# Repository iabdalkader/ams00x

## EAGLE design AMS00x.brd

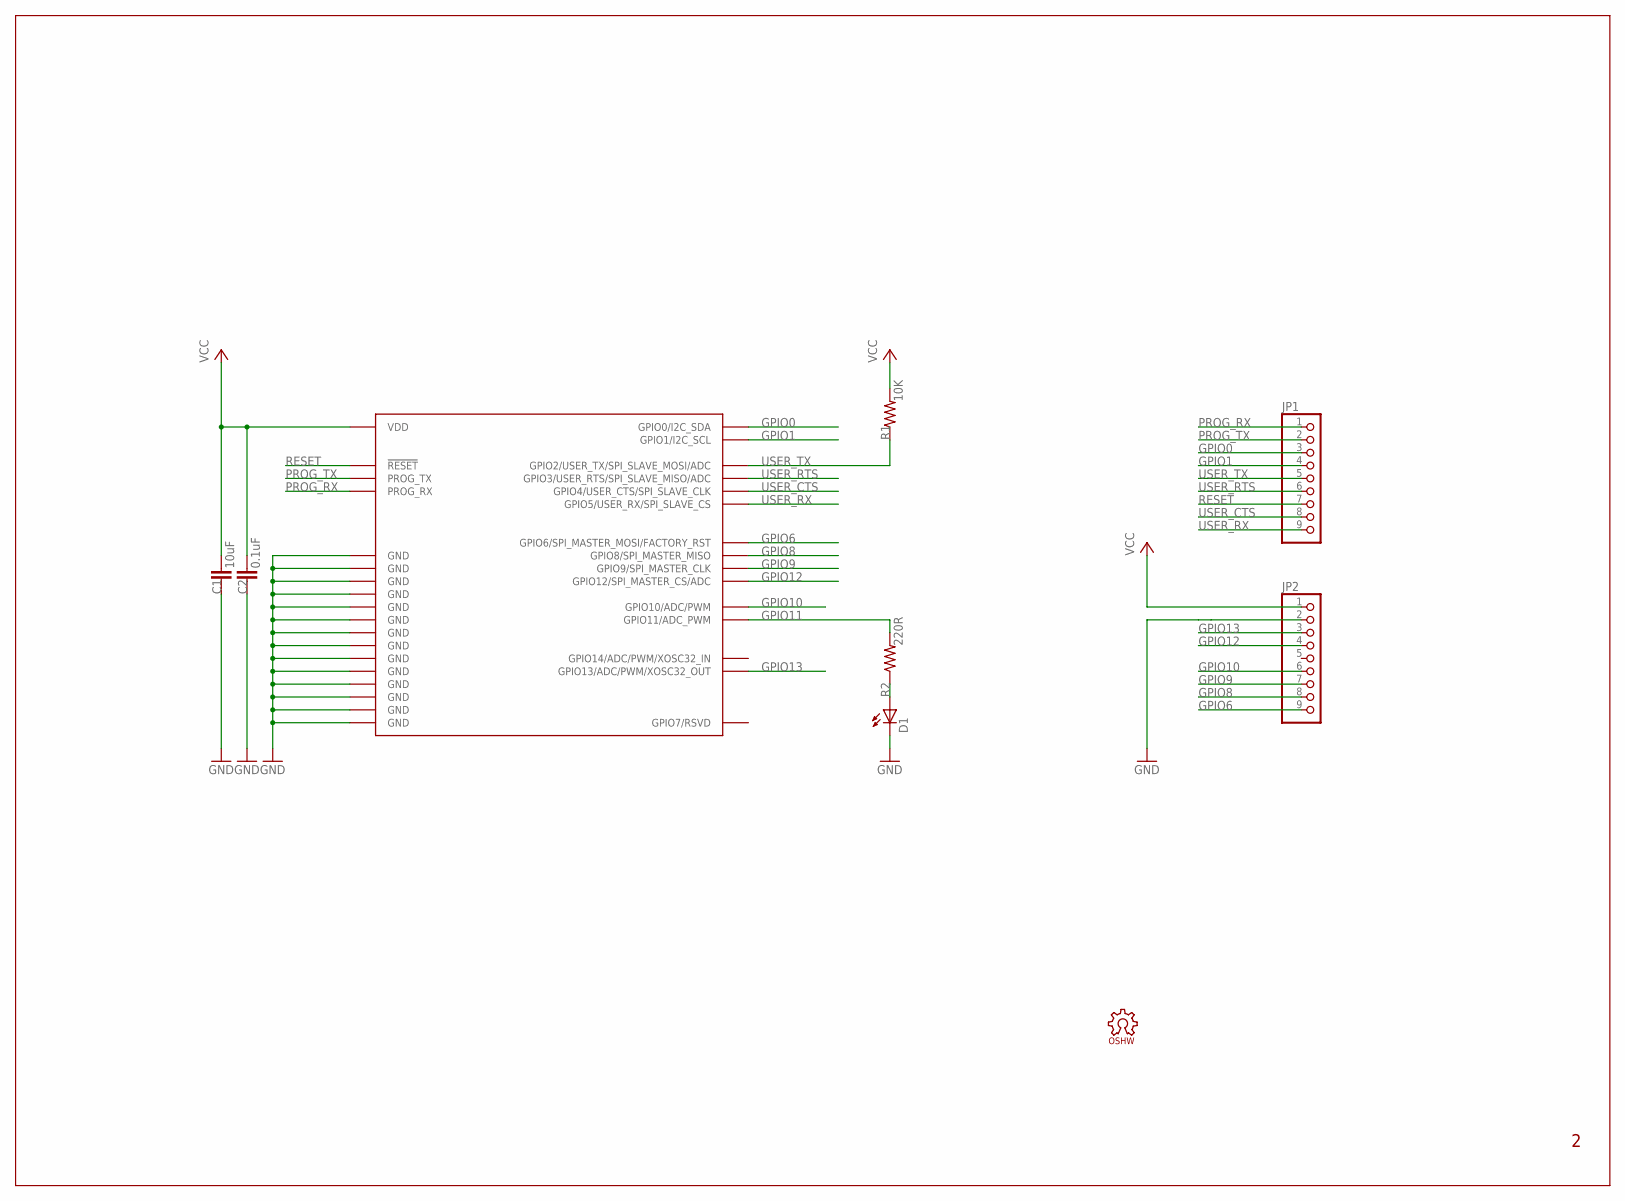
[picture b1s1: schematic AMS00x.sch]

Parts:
C1: 10uF; 0603-CAP
C2: 0.1uF; 0603-CAP
D1: LED0603; LED-0603
JP1, JP2: PINHD-1X9; 1X09
LOGO1: OSHW_LOGO_6MILX0100-NT; OSHW_6X100_NOTEXT
R1: 10K; 0603-RES
R2: 220R; 0603-RES
U$3: AMS00X

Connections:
GND: C1.1, C2.1, D1.C, JP2.2, U$3.P$1 (GND), U$3.P$19 (GND), U$3.P$22 (GND), U$3.P$23 (GND), U$3.P$24 (GND), U$3.P$25 (GND), U$3.P$26 (GND), U$3.P$27 (GND), U$3.P$28 (GND), U$3.P$29 (GND), U$3.P$30 (GND), U$3.P$31 (GND), U$3.P$32 (GND), U$3.P$33 (GND)
GPIO0: JP1.3, U$3.P$4 (GPIO0/I2C_SDA)
GPIO1: JP1.4, U$3.P$5 (GPIO1/I2C_SCL)
GPIO6: JP2.9, U$3.P$11 (GPIO6/SPI_MASTER_MOSI/FACTORY_RST)
GPIO8: JP2.8, U$3.P$13 (GPIO8/SPI_MASTER_MISO)
GPIO9: JP2.7, U$3.P$14 (GPIO9/SPI_MASTER_CLK)
GPIO10: JP2.6, U$3.P$15 (GPIO10/ADC/PWM)
GPIO11: R2.2, U$3.P$16 (GPIO11/ADC_PWM)
GPIO12: JP2.4, U$3.P$17 (GPIO12/SPI_MASTER_CS/ADC)
GPIO13: JP2.3, U$3.P$18 (GPIO13/ADC/PWM/XOSC32_OUT)
unnamed: D1.A, R2.1
PROG_RX: JP1.1, U$3.P$2 (PROG_RX)
PROG_TX: JP1.2, U$3.P$3 (PROG_TX)
RESET: JP1.7, U$3.P$8 (!RESET)
USER_CTS: JP1.8, U$3.P$9 (GPIO4/USER_CTS/SPI_SLAVE_CLK)
USER_RTS: JP1.6, U$3.P$7 (GPIO3/USER_RTS/SPI_SLAVE_MISO/ADC)
USER_RX: JP1.9, U$3.P$10 (GPIO5/USER_RX/SPI_SLAVE_CS)
USER_TX: JP1.5, R1.1, U$3.P$6 (GPIO2/USER_TX/SPI_SLAVE_MOSI/ADC)
VCC: C1.2, C2.2, JP2.1, R1.2, U$3.P$21 (VDD)

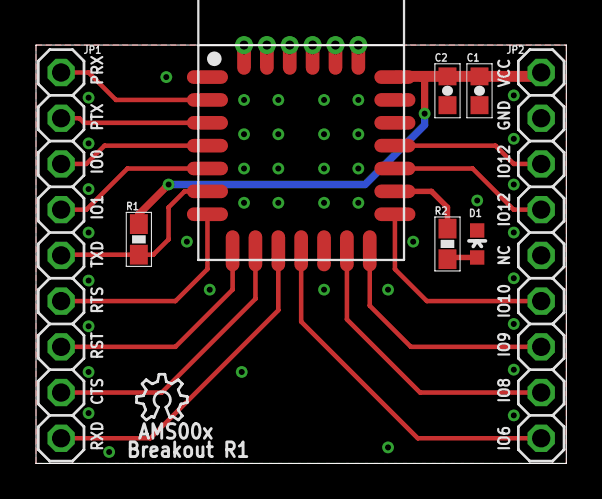
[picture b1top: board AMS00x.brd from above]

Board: 2 copper layers, 29.5 x 23.2 mm, 9 parts (0 on the bottom side), 19 nets.

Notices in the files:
AMS00x.sch:
Copyright (c) 2013 Ibrahim Abdalkader
This work is licensed under the Creative Commons Attribution-ShareAlike 3.0 License.
To view a copy of this license, visit http://creativecommons.org/licenses/by-sa/3.0
